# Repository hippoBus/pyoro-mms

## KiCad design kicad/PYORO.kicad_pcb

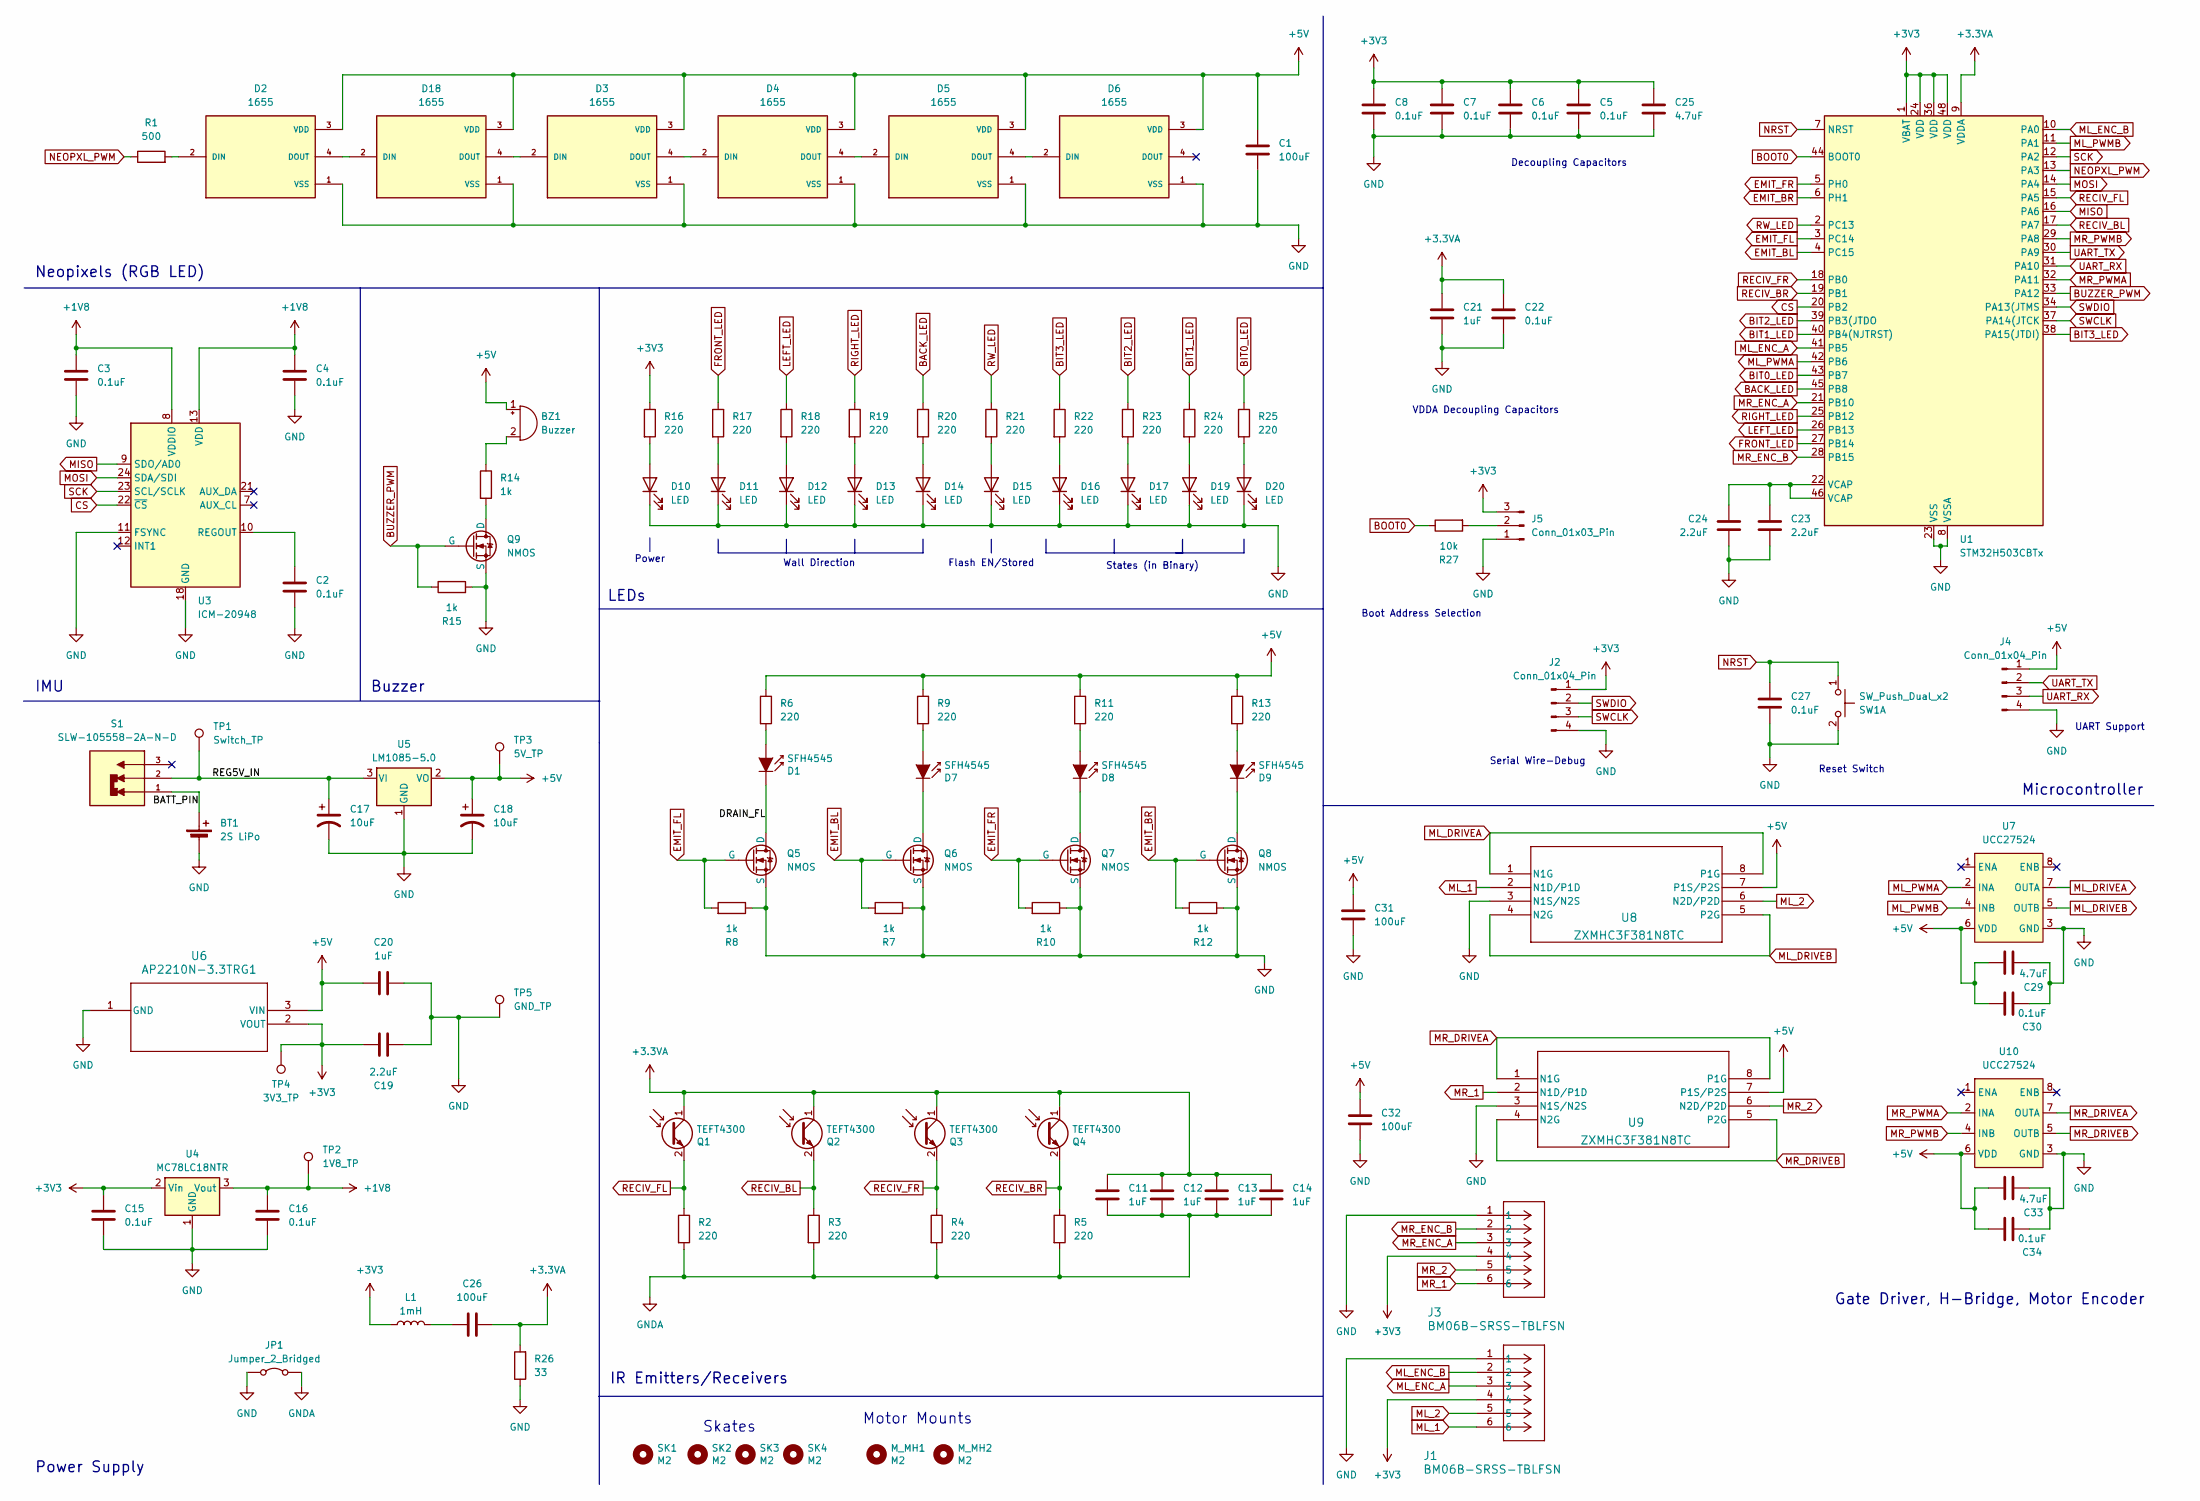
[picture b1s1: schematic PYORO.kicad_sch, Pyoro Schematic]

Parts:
BT1: 2S LiPo; PinHeader_1x02_P1.00mm_Vertical
BZ1: Buzzer; Buzzer_12x9.5RM7.6
C1, C26, C31, C32: 100uF; CP_Radial_D5.0mm_P2.00mm
C2, C3, C4, C5, C6, C7, C8, C15, C16, C22, C27, C30, C34: 0.1uF; C_1206_3216Metric_Pad1.33x1.80mm_HandSolder
C11, C12, C13, C14, C20, C21: 1uF; C_1206_3216Metric_Pad1.33x1.80mm_HandSolder
C17, C18: 10uF; CP_EIA-3216-18_Kemet-A_Pad1.58x1.35mm_HandSolder
C19, C23, C24: 2.2uF; C_0603_1608Metric_Pad1.08x0.95mm_HandSolder
C25, C29, C33: 4.7uF; C_0603_1608Metric_Pad1.08x0.95mm_HandSolder
D1, D7, D8, D9: SFH4545; Emitter
D2, D3, D4, D5, D6, D18: 1655; LED_1655; PARTREV 01
D10, D11, D12, D13, D14, D15, D16, D17, D19, D20: LED; LED_1206_3216Metric_Pad1.42x1.75mm_HandSolder
J1, J3: BM06B-SRSS-TBLFSN; CONN_BM06B-SRSS-TB_JST
J2, J4: Conn_01x04_Pin; PinHeader_1x04_P1.00mm_Vertical
J5: Conn_01x03_Pin; PinHeader_1x03_P1.00mm_Vertical
JP1: Jumper_2_Bridged; SolderJumper-2_P1.3mm_Bridged_Pad1.0x1.5mm
L1: 1mH; L_1008_2520Metric_Pad1.43x2.20mm_HandSolder
M_MH1, M_MH2: M2; Motor_mouse
Q1, Q2, Q3, Q4: TEFT4300; Emitter
Q5, Q6, Q7, Q8, Q9: NMOS; SOT-23
R1: 500; R_0603_1608Metric_Pad0.98x0.95mm_HandSolder
R2, R3, R4, R5, R6, R9, R11, R13, R16, R17, R18, R19, R20, R21, R22, R23, R24, R25: 220; R_0603_1608Metric_Pad0.98x0.95mm_HandSolder
R7, R8, R10, R12, R14, R15: 1k; R_0603_1608Metric_Pad0.98x0.95mm_HandSolder
R26: 33; R_0805_2012Metric_Pad1.20x1.40mm_HandSolder
R27: 10k; R_1206_3216Metric_Pad1.30x1.75mm_HandSolder
S1: SLW-105558-2A-N-D; SW_SLW-105558-2A-N-D; PARTREV 1.01
SK1, SK2, SK3, SK4: M2; MountingHole_2.2mm_M2
SW1: SW_Push_Dual_x2; SW_SPST_REED_CT05-XXXX-G1
TP1: Switch_TP; PinHeader_1x01_P1.00mm_Vertical
TP2: 1V8_TP; PinHeader_1x01_P1.00mm_Vertical
TP3: 5V_TP; PinHeader_1x01_P1.00mm_Vertical
TP4: 3V3_TP; PinHeader_1x01_P1.00mm_Vertical
TP5: GND_TP; PinHeader_1x01_P1.00mm_Vertical
U1: STM32H503CBTx; LQFP-48_7x7mm_P0.5mm
U3: ICM-20948; InvenSense_QFN-24_3x3mm_P0.4mm
U4: MC78LC18NTR; SOT-23-5
U5: LM1085-5.0; 5V Voltage Reg
U6: AP2210N-3.3TRG1; SOT-23W
U7, U10: UCC27524; DSD8_2P15X1P2
U8, U9: ZXMHC3F381N8TC; SOIC-8_3.9x4.9mm_P1.27mm

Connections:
+1V8: C3.2, C4.2, C16.1, TP2.1, U3.8 (VDDIO), U3.13 (VDD), U4.3 (Vout)
+3.3VA: C11.1, C12.1, C13.1, C14.1, C21.1, C22.1, C26.2, Q1.1 (C), Q2.1 (C), Q3.1 (C), Q4.1 (C), R26.2, U1.9 (VDDA)
+3V3: C5.1, C6.1, C7.1, C8.1, C15.1, C19.2, C25.1, J1.4, J2.1, J3.4, J5.3, L1.1, R16.1, TP4.1, U1.1 (VBAT), U1.24 (VDD), U1.36 (VDD), U1.48 (VDD), U4.2 (Vin), U6.2 (VOUT)
+5V: BZ1.1 (+), C1.1, C18.1, C20.1, C29.2, C30.2, C31.1, C32.1, C33.2, C34.2, D2.3 (VDD), D3.3 (VDD), D4.3 (VDD), D5.3 (VDD), D6.3 (VDD), D18.3 (VDD), J4.1, R6.1, R9.1, R11.1, R13.1, TP3.1, U5.2 (VO), U6.3 (VIN), U7.6 (VDD), U8.7 (P1S/P2S), U9.7 (P1S/P2S), U10.6 (VDD)
/BATT_PIN: BT1.1 (+), S1.1
/DRAIN_FL: D1.1 (K), Q5.1 (D)
/REG5V_IN: C17.1, S1.2, TP1.1, U5.3 (VI)
BACK_LED: R20.1, U1.45 (PB8)
BIT0_LED: R25.1, U1.43 (PB7)
BIT1_LED: R24.1, U1.40 (PB4(NJTRST))
BIT2_LED: R23.1, U1.39 (PB3(JTDO)
BIT3_LED: R22.1, U1.38 (PA15(JTDI))
BOOT0: R27.1, U1.44 (BOOT0)
BUZZER_PWM: Q9.2 (G), R15.1, U1.33 (PA12)
CS: U1.20 (PB2), U3.22 (~CS)
EMIT_BL: Q6.2 (G), R7.2, U1.4 (PC15)
EMIT_BR: Q8.2 (G), R12.2, U1.6 (PH1)
EMIT_FL: Q5.2 (G), R8.2, U1.3 (PC14)
EMIT_FR: Q7.2 (G), R10.2, U1.5 (PH0)
FRONT_LED: R17.1, U1.27 (PB14)
GND: BT1.2 (-), C1.2, C2.2, C3.1, C4.1, C5.2, C6.2, C7.2, C8.2, C15.2, C16.2, C17.2, C18.2, C19.1, C20.2, C21.2, C22.2, C23.2, C24.2, C25.2, C27.2, C29.1, C30.1, C31.2, C32.2, C33.1, C34.1, D2.1 (VSS), D3.1 (VSS), D4.1 (VSS), D5.1 (VSS), D6.1 (VSS), D10.1 (K), D11.1 (K), D12.1 (K), D13.1 (K), D14.1 (K), D15.1 (K), D16.1 (K), D17.1 (K), D18.1 (VSS), D19.1 (K), D20.1 (K), J1.1, J2.4, J3.1, J4.4, J5.1, JP1.1 (A), Q5.3 (S), Q6.3 (S), Q7.3 (S), Q8.3 (S), Q9.3 (S), R7.1, R8.1, R10.1, R12.1, R15.2, R26.1, SW1.2 (D), TP5.1, U1.8 (VSSA), U1.23 (VSS), U1.35 (VSS), U1.47 (VSS), U3.11 (FSYNC), U3.18 (GND), U3.20 (GND), U4.1 (GND), U5.1 (GND), U6.1 (GND), U7.3 (GND), U8.3 (N1S/N2S), U9.3 (N1S/N2S), U10.3 (GND)
GNDA: C11.2, C12.2, C13.2, C14.2, JP1.2 (B), R2.2, R3.2, R4.2, R5.2
LEFT_LED: R18.1, U1.26 (PB13)
MISO: U1.16 (PA6), U3.9 (SDO/AD0)
ML_1: J1.6, U8.2 (N1D/P1D)
ML_2: J1.5, U8.6 (N2D/P2D)
ML_DRIVEA: U7.7 (OUTA), U8.1 (N1G), U8.8 (P1G)
ML_DRIVEB: U7.5 (OUTB), U8.4 (N2G), U8.5 (P2G)
ML_ENC_A: J1.3, U1.41 (PB5)
ML_ENC_B: J1.2, U1.10 (PA0)
ML_PWMA: U1.42 (PB6), U7.2 (INA)
ML_PWMB: U1.11 (PA1), U7.4 (INB)
MOSI: U1.14 (PA4), U3.24 (SDA/SDI)
MR_1: J3.6, U9.2 (N1D/P1D)
MR_2: J3.5, U9.6 (N2D/P2D)
MR_DRIVEA: U9.1 (N1G), U9.8 (P1G), U10.7 (OUTA)
MR_DRIVEB: U9.4 (N2G), U9.5 (P2G), U10.5 (OUTB)
MR_ENC_A: J3.3, U1.21 (PB10)
MR_ENC_B: J3.2, U1.28 (PB15)
MR_PWMA: U1.32 (PA11), U10.2 (INA)
MR_PWMB: U1.29 (PA8), U10.4 (INB)
NEOPXL_PWM: R1.1, U1.13 (PA3)
NRST: C27.1, SW1.1 (C), U1.7 (NRST)
unnamed: BZ1.2 (-), R14.1
unnamed: C23.1, C24.1, U1.22 (VCAP), U1.46 (VCAP)
unnamed: C26.1, L1.2
unnamed: D1.2 (A), R6.2
unnamed: D2.2 (DIN), R1.2
unnamed: D3.4 (DOUT), D4.2 (DIN)
unnamed: D4.4 (DOUT), D5.2 (DIN)
unnamed: D5.4 (DOUT), D6.2 (DIN)
unnamed: D7.2 (A), R9.2
unnamed: D7.1 (K), Q6.1 (D)
unnamed: D8.2 (A), R11.2
unnamed: D8.1 (K), Q7.1 (D)
unnamed: D9.2 (A), R13.2
unnamed: D9.1 (K), Q8.1 (D)
unnamed: D10.2 (A), R16.2
unnamed: D11.2 (A), R17.2
unnamed: D12.2 (A), R18.2
unnamed: D13.2 (A), R19.2
unnamed: D14.2 (A), R20.2
unnamed: D15.2 (A), R21.2
unnamed: D16.2 (A), R22.2
unnamed: D17.2 (A), R23.2
unnamed: D2.4 (DOUT), D18.2 (DIN)
unnamed: D3.2 (DIN), D18.4 (DOUT)
unnamed: D19.2 (A), R24.2
unnamed: D20.2 (A), R25.2
unnamed: J5.2, R27.2
unnamed: Q9.1 (D), R14.2
unnamed: C2.1, U3.10 (REGOUT)
RECIV_BL: Q2.2 (E), R3.1, U1.17 (PA7)
RECIV_BR: Q4.2 (E), R5.1, U1.19 (PB1)
RECIV_FL: Q1.2 (E), R2.1, U1.15 (PA5)
RECIV_FR: Q3.2 (E), R4.1, U1.18 (PB0)
RIGHT_LED: R19.1, U1.25 (PB12)
RW_LED: R21.1, U1.2 (PC13)
SCK: U1.12 (PA2), U3.23 (SCL/SCLK)
SWCLK: J2.3, U1.37 (PA14(JTCK)
SWDIO: J2.2, U1.34 (PA13(JTMS)
UART_RX: J4.3, U1.31 (PA10)
UART_TX: J4.2, U1.30 (PA9)

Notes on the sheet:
Power Supply
Neopixels (RGB LED)
LEDs
States (in Binary)
VDDA Decoupling Capacitors
Wall Direction
UART Support
Flash EN/Stored
Buzzer
Skates
Boot Address Selection
Motor Mounts
Power
IMU
Serial Wire-Debug
Reset Switch
Gate Driver, H-Bridge, Motor Encoder
Decoupling Capacitors
IR Emitters/Receivers
Microcontroller

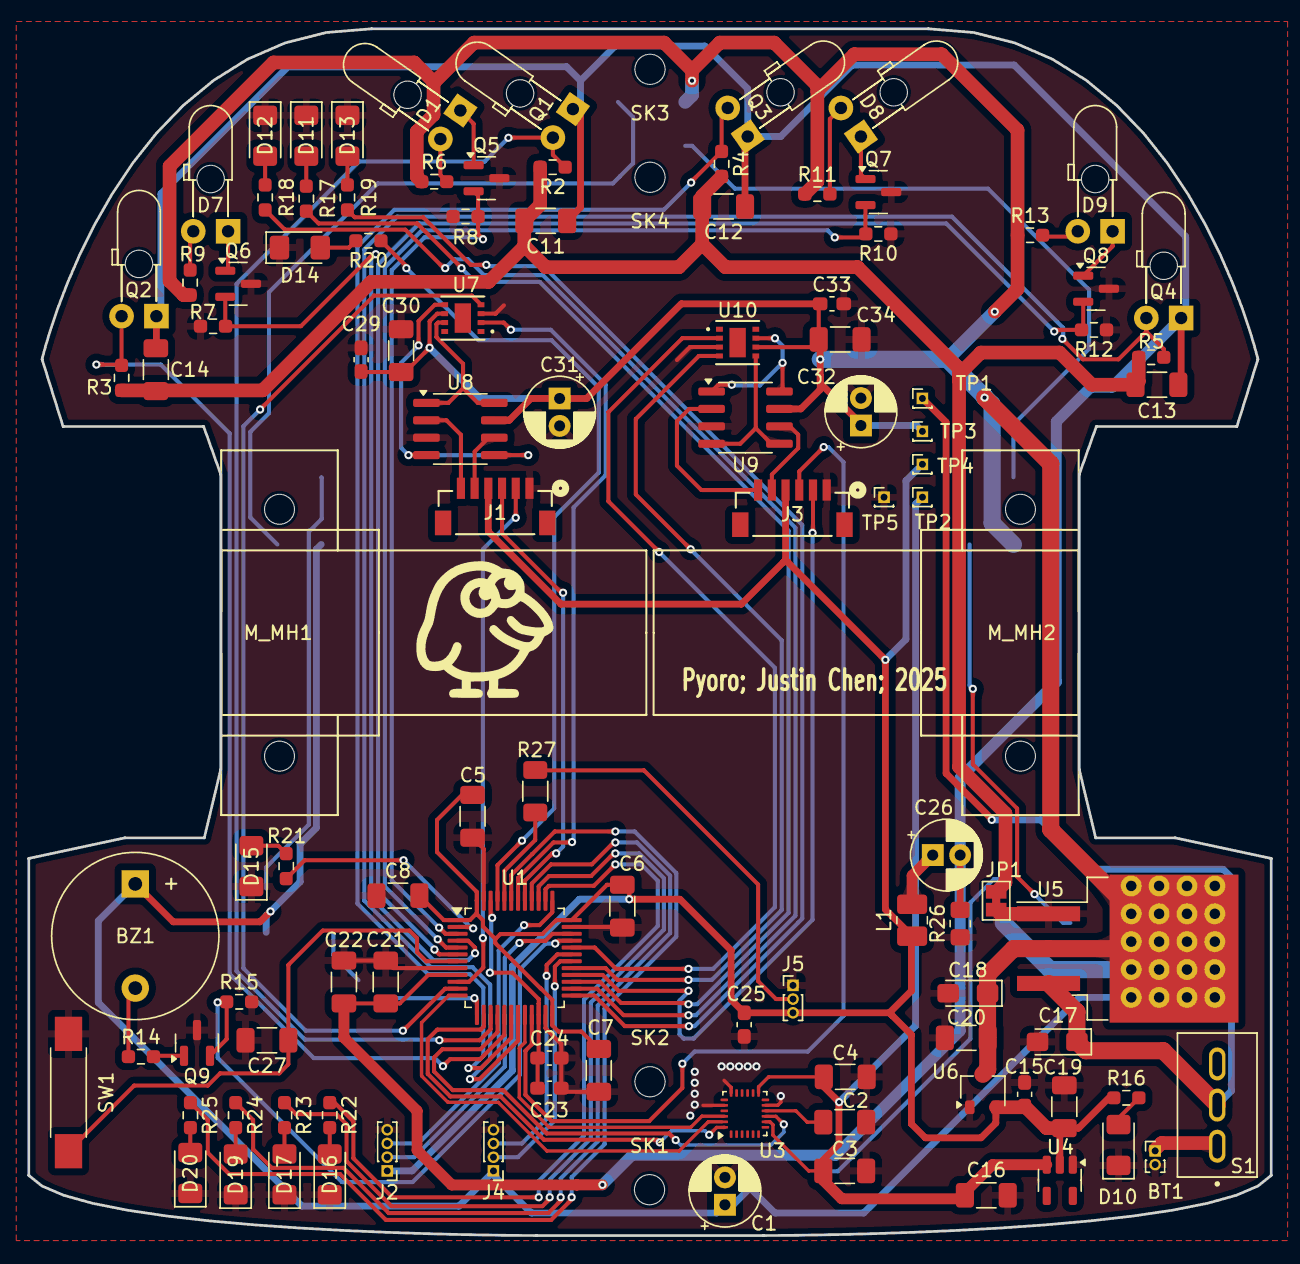
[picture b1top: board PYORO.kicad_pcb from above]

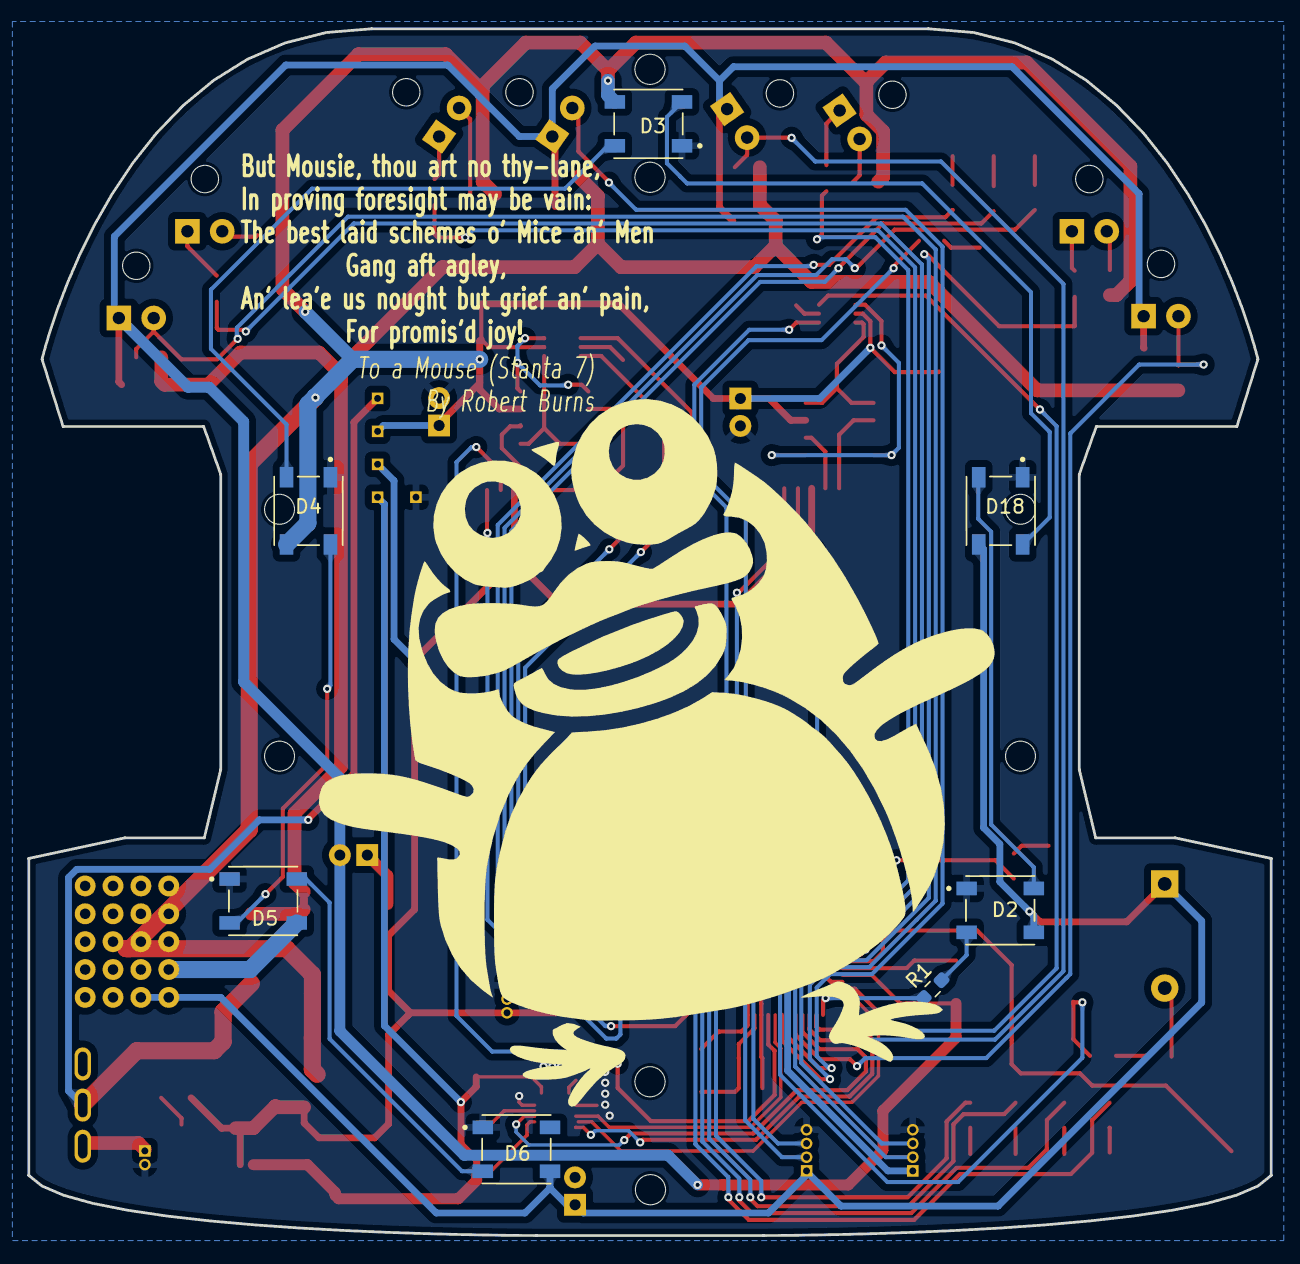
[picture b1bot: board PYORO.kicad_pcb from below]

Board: 2 copper layers, 90.6 x 88.0 mm, 118 parts (7 on the bottom side), 83 nets.

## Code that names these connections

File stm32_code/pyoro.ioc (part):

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Mcu.Name=STM32H503CBTx
Mcu.Package=LQFP48
Mcu.UserName=STM32H503CBTx
PA0.GPIOParameters=GPIO_Label
PA0.GPIO_Label=ML_ENC_B
PA0.Mode=Encoder_mode_occur1
PA0.Signal=LPTIM1_IN2
PA1.GPIOParameters=GPIO_Label
PA1.GPIO_Label=ML_PWMB
PA1.Signal=S_TIM1_CH3
PA10.Mode=Asynchronous
PA10.Signal=USART1_RX
PA11.GPIOParameters=GPIO_Label
PA11.GPIO_Label=MR_PWMA
PA11.Signal=S_TIM1_CH4
PA12.GPIOParameters=GPIO_Label
PA12.GPIO_Label=BUZZER_PWM
PA12.Signal=S_TIM3_CH4
PA13(JTMS/SWDIO).GPIOParameters=GPIO_Label
PA13(JTMS/SWDIO).GPIO_Label=SWDIO
PA13(JTMS/SWDIO).Mode=Serial_Wire
PA13(JTMS/SWDIO).Signal=DEBUG_JTMS-SWDIO
PA14(JTCK/SWCLK).GPIOParameters=GPIO_Label
PA14(JTCK/SWCLK).GPIO_Label=SWCLK
PA14(JTCK/SWCLK).Mode=Serial_Wire
PA14(JTCK/SWCLK).Signal=DEBUG_JTCK-SWCLK
PA15(JTDI).GPIOParameters=GPIO_Label
PA15(JTDI).GPIO_Label=BIT3_LED
PA15(JTDI).Signal=GPIO_Output
PA2.Mode=Full_Duplex_Master
PA2.Signal=SPI1_SCK
PA3.GPIOParameters=GPIO_Label
PA3.GPIO_Label=NEOPXL_PWM
PA3.Signal=S_TIM2_CH4
PA4.Mode=Full_Duplex_Master
PA4.Signal=SPI1_MOSI
PA5.GPIOParameters=GPIO_Label
PA5.GPIO_Label=RECIV_FL
PA5.Signal=ADCx_INP19
PA6.Mode=Full_Duplex_Master
PA6.Signal=SPI1_MISO
PA7.GPIOParameters=GPIO_Label
PA7.GPIO_Label=RECIV_BL
PA7.Signal=ADCx_INP7
PA8.GPIOParameters=GPIO_Label
PA8.GPIO_Label=MR_PWMB
PA8.Signal=S_TIM1_CH1
PA9.Mode=Asynchronous
PA9.Signal=USART1_TX
PB0.GPIOParameters=GPIO_Label
PB0.GPIO_Label=RECIV_FR
PB0.Signal=ADCx_INP9
PB1.GPIOParameters=GPIO_Label
PB1.GPIO_Label=RECIV_BR
PB1.Signal=ADCx_INP5
PB10.GPIOParameters=GPIO_Label
PB10.GPIO_Label=MR_ENC_A
PB10.Mode=Encoder_mode_occur1
PB10.Signal=LPTIM2_IN1
PB12.GPIOParameters=GPIO_Label
PB12.GPIO_Label=RIGHT_LED
PB12.Signal=GPIO_Output
PB13.GPIOParameters=GPIO_Label
PB13.GPIO_Label=LEFT_LED
PB13.Signal=GPIO_Output
PB14.GPIOParameters=GPIO_Label
PB14.GPIO_Label=FRONT_LED
PB14.Signal=GPIO_Output
PB15.GPIOParameters=GPIO_Label
PB15.GPIO_Label=MR_ENC_B
PB15.Mode=Encoder_mode_occur1
PB15.Signal=LPTIM2_IN2
PB2.GPIOParameters=GPIO_Label
PB2.GPIO_Label=SPI1_CS
PB2.Signal=GPIO_Output
PB3(JTDO/TRACESWO).GPIOParameters=GPIO_Label
PB3(JTDO/TRACESWO).GPIO_Label=BIT2_LED
PB3(JTDO/TRACESWO).Signal=GPIO_Output
PB4(NJTRST).GPIOParameters=GPIO_Label
PB4(NJTRST).GPIO_Label=BIT1_LED
PB4(NJTRST).Signal=GPIO_Output
PB5.GPIOParameters=GPIO_Label
PB5.GPIO_Label=ML_ENC_A
PB5.Mode=Encoder_mode_occur1
PB5.Signal=LPTIM1_IN1
PB6.GPIOParameters=GPIO_Label
PB6.GPIO_Label=ML_PWMA
PB6.Signal=S_TIM1_CH2
PB7.GPIOParameters=GPIO_Label
PB7.GPIO_Label=BIT0_LED
PB7.Signal=GPIO_Output
PB8.GPIOParameters=GPIO_Label
PB8.GPIO_Label=BACK_LED
PB8.Signal=GPIO_Output
PC13.GPIOParameters=GPIO_Label
PC13.GPIO_Label=RW_LED
PC13.Signal=GPIO_Output
PC14-OSC32_IN(OSC32_IN).GPIOParameters=GPIO_Label
PC14-OSC32_IN(OSC32_IN).GPIO_Label=EMIT_FL
PC14-OSC32_IN(OSC32_IN).Signal=GPIO_Output
PC15-OSC32_OUT(OSC32_OUT).GPIOParameters=GPIO_Label
PC15-OSC32_OUT(OSC32_OUT).GPIO_Label=EMIT_BL
PC15-OSC32_OUT(OSC32_OUT).Signal=GPIO_Output
PH0-OSC_IN(PH0).GPIOParameters=GPIO_Label
PH0-OSC_IN(PH0).GPIO_Label=EMIT_FR
PH0-OSC_IN(PH0).Signal=GPIO_Output
PH1-OSC_OUT(PH1).GPIOParameters=GPIO_Label
PH1-OSC_OUT(PH1).GPIO_Label=EMIT_BR
PH1-OSC_OUT(PH1).Signal=GPIO_Output
RCC.HSE_VALUE=25000000
RCC.SYSCLKFreq_VALUE=32000000
board=custom

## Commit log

2025-06-30 Reconfigured .gitignore
2025-06-30 Initialize KiCad project
2025-07-08 Imported majority of compoents in KiCad
2025-07-14 Setup stm32CubeIDE project
2025-07-14 Started IMU circuit
2025-07-21 Started motor controller
2025-07-22 Started 6-pin JST Headers
2025-07-23 Started IR Receivers, and changed pin assignment
2025-07-31 Started IR Emitters, and enable MCU flash
2025-08-02 Started Buzzer
2025-08-04 Started voltage regulators
2025-08-05 Added Neopixel PWM pin, and reoganized schematic
2025-08-05 Started LEDs for the extra GPIO pins
2025-08-07 Added new test points, updated missing Capacitor and Resistor values, fix MCU power supply scheme
2025-08-08 Added Filtering for 3.3VA
2025-08-18 Fixed spelling errors
2025-08-18 Converted capacitor units
2025-09-21 Added new symbols for silkscreen and IMU backup
2025-09-21 Fix some schematics error, and define resistor values
2025-11-12 Added UART support incase
2025-11-13 Add the remaining stm32 drivers incase
2025-11-27 Modified LEDs, started Gate Driver, change H-Bridge
2025-11-28 Removed Enable pins for H-Bridge
2025-11-29 Added 2 PWM channels for motors, and moved from UART3 to UART1
2025-11-29 Moved Motor PWM gen. to TIM1, and moved pin assignments
2025-11-29 Completed pin assignments
2025-11-30 Added BOM, and finalized RLC Bandpass filter
2025-11-30 Moved all 4 PWM Generations to seperate channels
2025-12-10 Finish importing BOM parts and footprint assignment
2025-12-11 Added skate holes and motor mount holes
2025-12-12 Setup edgecuts, and Board Setup
2025-12-12 Started Pwr Supply layout
2025-12-12 Changed graphic fonts
2025-12-13 Added IMU to layout
2025-12-13 Added motor drivers to layout
2025-12-13 Added IR layout, and modified symbols for IR
2025-12-15 Added stm32 to layout
2025-12-15 Added skates
2025-12-16 Add wall direction LEDs to layout
2025-12-17 Added binary state LEDs
2025-12-17 Added neopixels
2025-12-17 Added testpoints to layout
2025-12-17 Finalized silkscreen, and fix remaining DRC
2025-12-17 Added teardrops
2025-12-17 Removed extra footprints, fixed silkscreen
2025-12-18 Fixed fonts that did not match the rest
